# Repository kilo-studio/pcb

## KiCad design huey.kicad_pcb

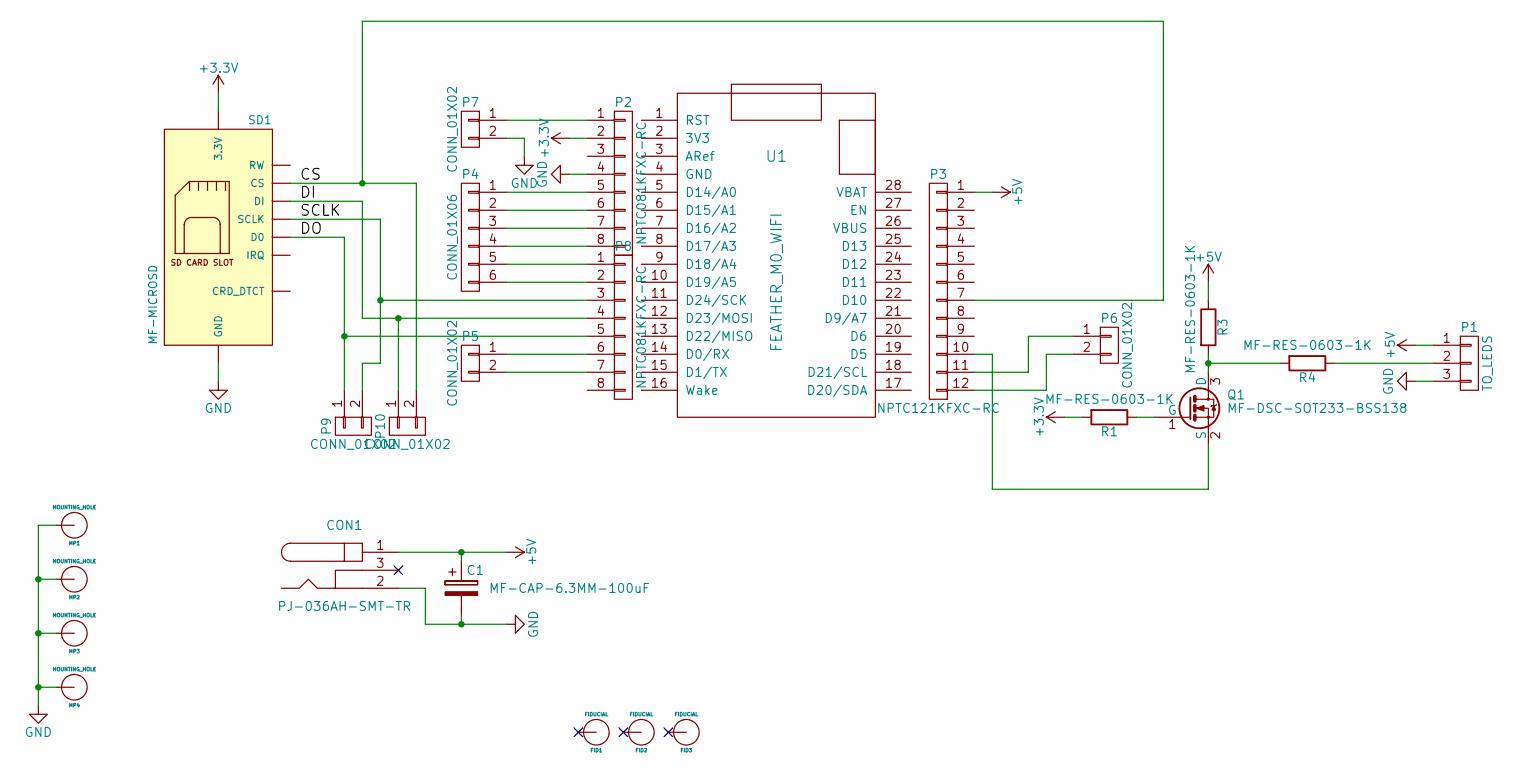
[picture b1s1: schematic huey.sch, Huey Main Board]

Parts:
C1: MF-CAP-6.3MM-100uF; MF_Passives-CP6.3MM
CON1: PJ-036AH-SMT-TR; Digikey Part CP-036AHPJCT-ND
FID1, FID2, FID3: FIDUCIAL; Fiducial_1mm_Dia_2.54mm_Outer_CopperTop
MP1, MP2, MP3, MP4: MOUNTING_HOLE; MOUNTING_HOLE_#4
P1: TO_LEDS; LED_BOARD_CONNECTOR
P2, P8: NPTC081KFXC-RC; FEMALE_HEADER_8x1_SMD
P3: NPTC121KFXC-RC; FEMALE_HEADER_12x1_SMD; Digikey S5604-ND
P4: CONN_01X06; Pin_Header_Straight_1x06
P5, P6, P7, P9, P10: CONN_01X02; Pin_Header_Straight_1x02
Q1: MF-DSC-SOT233-BSS138; MF_Discrete_Semiconductor-SOT-23-3
R1, R3, R4: MF-RES-0603-1K; R_0603
SD1: MF-MICROSD; MF_Connectors-MF-MICROSD
U1: FEATHER_M0_WIFI; Adafruit_Feather_M0_WiFi

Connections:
+3V3: P2.2, R1.2, SD1.4 (3.3V)
+5V: C1.1, CON1.1, P1.1, P3.1, R3.1
/CS: P3.7, P10.2, SD1.2 (CS)
/DI: P8.4, P10.1, SD1.3 (DI)
/DO: P8.5, P9.1, SD1.7 (D0)
/SCLK: P8.3, P9.2, SD1.5 (SCLK)
GND: C1.2, CON1.2, MP1.1, MP2.1, MP3.1, MP4.1, P1.3, P2.4, P7.2, SD1.6 (GND), SD1.G0 (GND), SD1.G1 (GND)
unnamed: P1.2, R4.1
unnamed: P2.1, P7.1
unnamed: P2.5, P4.1
unnamed: P2.6, P4.2
unnamed: P2.7, P4.3
unnamed: P2.8, P4.4
unnamed: P3.10, Q1.2 (S)
unnamed: P3.11, P6.1
unnamed: P3.12, P6.2
unnamed: P4.5, P8.1
unnamed: P4.6, P8.2
unnamed: P5.1, P8.6
unnamed: P5.2, P8.7
unnamed: Q1.1 (G), R1.1
unnamed: Q1.3 (D), R3.2, R4.2
unnamed: SD1.9 (CRD_DTCT), SD1.10 (CRD_DTCT)

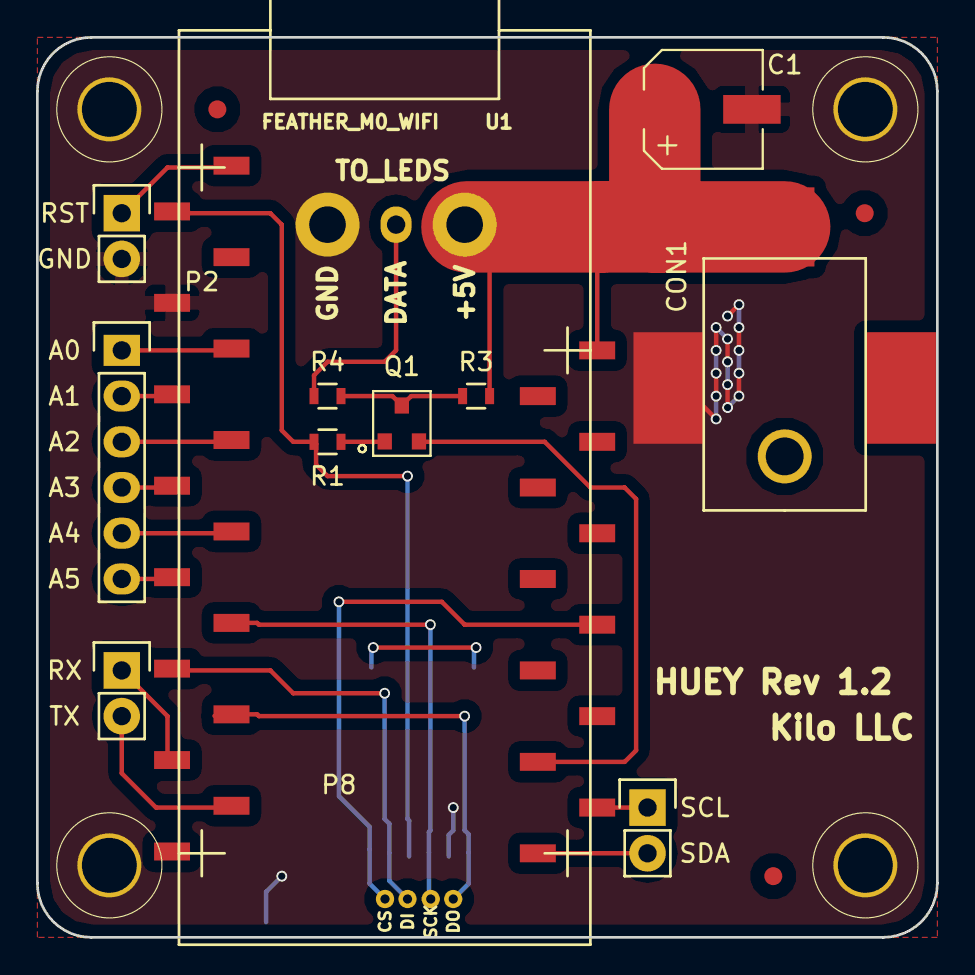
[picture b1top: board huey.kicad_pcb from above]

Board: 2 copper layers, 50.0 x 50.0 mm, 25 parts (1 on the bottom side), 23 nets.

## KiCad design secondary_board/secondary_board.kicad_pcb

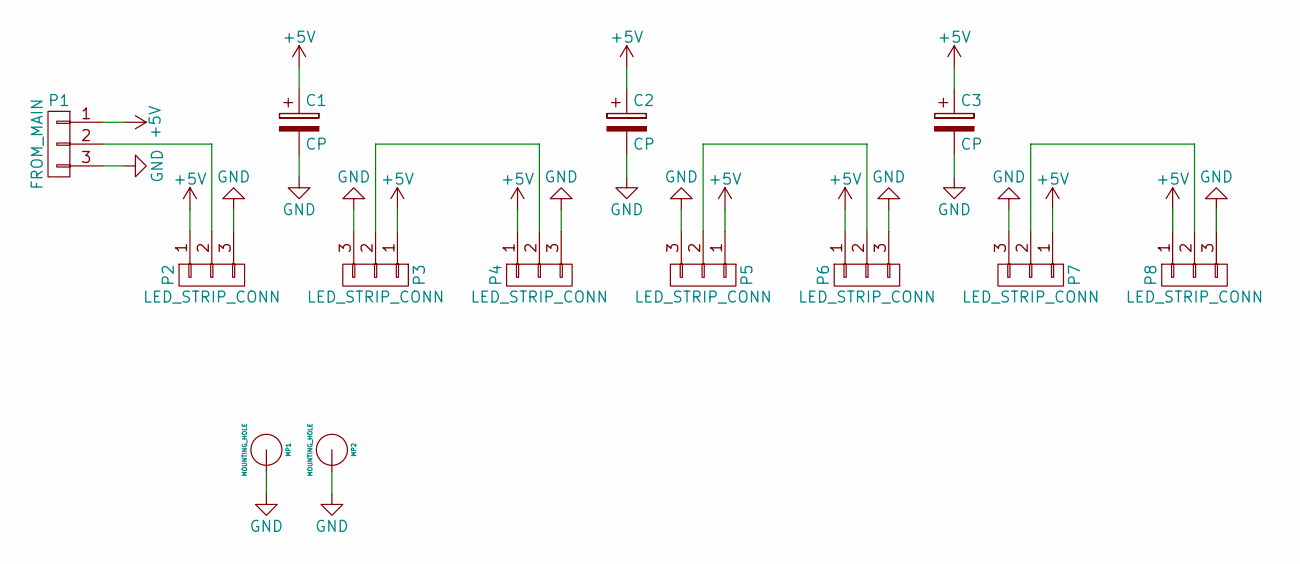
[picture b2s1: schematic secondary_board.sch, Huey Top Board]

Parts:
C1, C2, C3: CP; C_Radial_D10_L13_P5
MP1, MP2: MOUNTING_HOLE; MOUNTING_HOLE_#4
P1: FROM_MAIN; LED_BOARD_CONNECTOR
P2, P3, P4, P5, P6, P7, P8: LED_STRIP_CONN

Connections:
+5V: C1.1, C2.1, C3.1, P1.1, P2.1, P3.1, P4.1, P5.1, P6.1, P7.1, P8.1
GND: C1.2, C2.2, C3.2, MP1.1, MP2.1, P1.3, P2.3, P3.3, P4.3, P5.3, P6.3, P7.3, P8.3
unnamed: P1.2, P2.2
unnamed: P3.2, P4.2
unnamed: P5.2, P6.2
unnamed: P7.2, P8.2

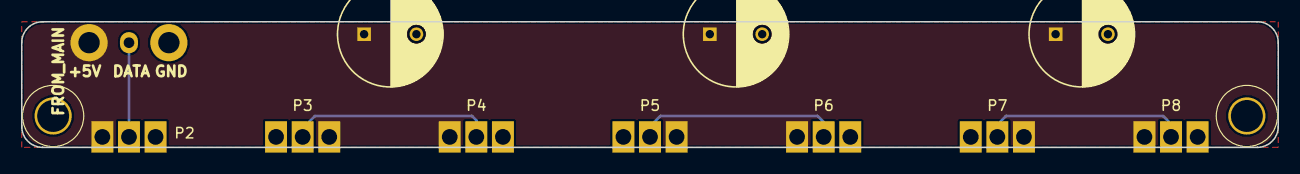
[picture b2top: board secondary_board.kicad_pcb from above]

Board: 2 copper layers, 120.0 x 12.0 mm, 13 parts (0 on the bottom side), 6 nets.

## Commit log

2018-04-08 starting layout
2018-04-09 I think rev 1.0 is looking good... submitted for approval.
2018-04-10 Some additions to the main board layout, and a new design of the top board.
2018-04-10 updating jack component
2018-04-10 adding 8x1 female header
2018-04-10 Pushing final changes for rev 1.0
2018-05-07 Revision 1.1
    Changelog:
    -Re-exported copper pours to correct issues in rev 1.0
    -Moved SD card to bottom for increased space
    -Increased the clearance of copper pours for easier visual verification
    -Added some vias to GND underneath the power jack to compensate for reduced GND plane area after increasing clearance
    -Added test points for SD card data access
2018-05-07 Updated PDF schematic
2018-05-28 Revision 1.1
    Changelog:
    - Removed R2 resistor from the logic level converter
2018-05-29 Changing 12x1 SMD header to 8x1 and 4x1 headers, for (hopefully) better part availability
